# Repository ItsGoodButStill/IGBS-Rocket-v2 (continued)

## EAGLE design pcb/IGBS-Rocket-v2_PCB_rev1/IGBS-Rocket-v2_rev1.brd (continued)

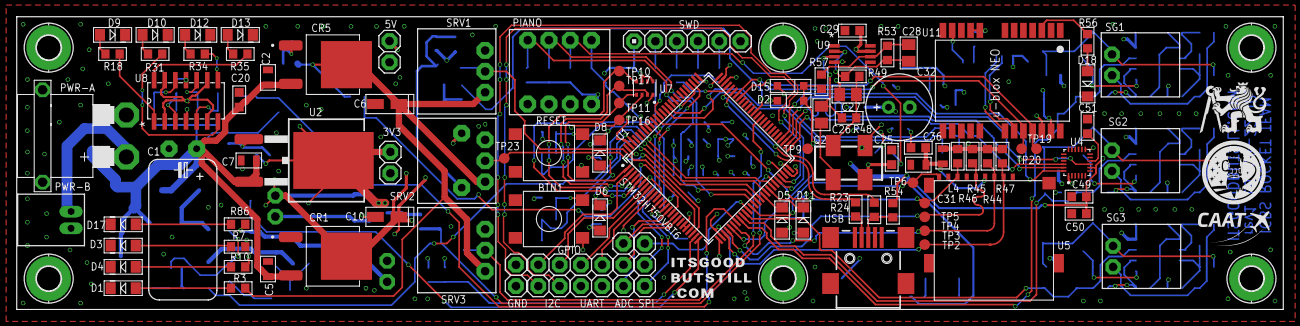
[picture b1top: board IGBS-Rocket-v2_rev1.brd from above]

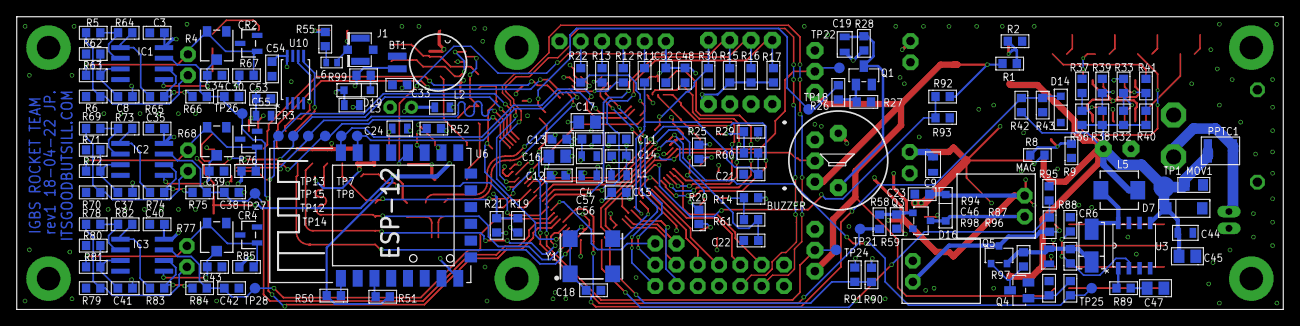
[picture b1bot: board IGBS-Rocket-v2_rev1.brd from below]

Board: 4 copper layers, 151.1 x 34.9 mm, 269 parts (164 on the bottom side), 154 nets.

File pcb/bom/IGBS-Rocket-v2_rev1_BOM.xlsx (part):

IGBS Rocket v2 (rev1)
 | Množství | Sklad | Hodnota | Název | Pouzdro | Součástky | Popis | Výrobce | Cena | Objednací číslo | Odkaz
 | 1 | 0 | STM32H750VBT6 | STM32H750VBT6 | LQFP100-14X14 | U1 | MCU | STM | 300 | Aliexpress | https://www.aliexpress.com/item/1005003610067060.html?spm=a2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
 | 1 | 0 | BMP280 | BMP280 | BMP280 | B1 | Modul - Barometr | Bosch | 21 | Aliexpress | https://www.aliexpress.com/item/32817286611.html?spm=a2g0o.9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
 | 1 | 5 | ESP-12E/F | ESP-12E/F | ESP-12E | U6 | Modul - ESP WiFi | Espressif | 32 | Aliexpress | https://www.aliexpress.com/item/32256161821.html?spm=a2g0o.9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
 | 1 | 1 | GY-NEO6MV2 | GY-NEO6MV2 | GY-NEO6MV2 | B6 | Modul - GPS | U-blox | 68 | Aliexpress | https://www.aliexpress.com/item/1005001635722164.html?spm=a2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
 | 1 | 1 | ICM-20948 | ICM-20948 | ICM-20948 | B2 | Modul - IMU 9-DOF | InvenSense | 471 | Aliexpress | https://www.aliexpress.com/wholesale?catId=0&initiative_id=S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
 | 3 | 5 | BF350 | BF350 | BF350 | B3, B4, B5 | Modul - Tenzometr | čína | 0 | Aliexpress | https://www.aliexpress.com/item/4000907686535.html?spm=a2g0o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
 | 1 | 1 | ENC-03 | ENC-03RC | ENC-03RC | Q2 | Gyroskop (analogový 1-osý) | Murata | 115 | 775-043 | https://www.gme.cz/modul-s-jednoosym-gyroskopem-analog-vystup
 | 1 | 0 | MCP6V51T-E/MS | MCP6V51T-E/MS | MSOP8 | U9 | OP Amp (1 kanál, nulovaný) | Microchip | 43 | 579-MCP6V51T-E/MS | https://cz.mouser.com/ProductDetail/Microchip-Technology/MCP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
 | 1 | 0 | LP324DRG4 | LP324DRG4D14 | SOIC-14 | U8 | OP Amp (4 kanál, low-power) | TI | 16 | 595-LP324DRG4 | https://cz.mouser.com/ProductDetail/Texas-Instruments/LP324D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
 | 3 | 0 | NCV21872DR2G | NCV21872DR2G | SOIC-8 | IC1,IC2,IC3 | OP Amp (2 kanál, precision) | Onsemi | 23 | 863-NCV21872DR2G | https://cz.mouser.com/ProductDetail/onsemi/NCV21872DR2G?qs=s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
 | 1 | 0 | 24MHz | OSCILLATOR | SMD-7X5-4PAD | Y1 | Oscilátor | IQD | 40 | 449-LFSPXO018541REEL | https://cz.mouser.com/ProductDetail/IQD/LFSPXO018541Reel?qs=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
 | 1 | 0 | LM317BD2TG | LM317BD2TG | TO-263-3 | U4 | Regulátor - 3.3 V 1.5A | Onsemi | 57 | 863-LM317BD2TG | https://cz.mouser.com/ProductDetail/onsemi/LM317BD2TG?qs=2Ot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
 | 1 | 0 | LD1117DT50 | LD1117DT50TRDPAK | TO-252-3 | CR1 | Regulátor - LDO 5V 1A | STM | 15 | 511-LD1117DT50-TR | https://cz.mouser.com/ProductDetail/STMicroelectronics/LD111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
 | 1 | 0 | AZ2185D | AZ2185D-ADJTRG1 | TO-252-3 | CR5 | Regulátor - LDO 6V 3A | Diodes Inc. | 12 | 621-AZ2185D-ADJTRG1 | https://cz.mouser.com/ProductDetail/Diodes-Incorporated/AZ21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
 | 1 | 0 | CS5171EDR8G | CS5171EDR8G | SOIC-8 | U3 | DC-DC Boost 12V 1.5 A | Onsemi | 12 | CS5171EDR8G | https://cz.farnell.com/on-semiconductor/cs5171edr8g/dc-dc-co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
 | 1 | 0 | BSS316N-H6327 | MOSFET-NCHANNEL | SOT23-3 | Q3 | Tranzistor (N-MOSFET) | Infineon | 10 | 726-BSS316NH6327XT | https://cz.mouser.com/ProductDetail/Infineon-Technologies/BS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
 | 1 | 0 | BSS314PE H6327 | MOSFET-PCHANNEL | SOT23-3 | Q5 | Tranzistor (P-MOSFET) | Infineon | 10 | 726-BSS314PEH6327XT | https://cz.mouser.com/ProductDetail/Infineon-Technologies/BS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
 | 2 | 0 | BC817 | BC817-16LT1SMD | SOT23-BEC | Q1 | Tranzistor (NPN) | NXP | 5 | 771-BC817-40-T/R | https://cz.mouser.com/ProductDetail/Nexperia/BC817-40215?qs=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
 | 1 | 0 | 1N4148 | DIODESOD123 | SOD-123 | D16 | Dioda | Vishay | 8 | 78-1N4148W-G3-08 | https://cz.mouser.com/ProductDetail/Vishay-Semiconductors/1N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
 | 1 | 0 | SS12 | DIODE SHOTTKY | DO-214 | CR16 | Shottkyho dioda | Onsemi | 9 | 512-SS12 | https://cz.mouser.com/ProductDetail/onsemi-Fairchild/SS12?qs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
 | 3 | 0 | 3V6 | DIODE-ZENER | SOD-123 | D14, D15 | Zenerova dioda 3.6V | NXP | 6 | 771-BZT52-B3V6X | https://cz.mouser.com/ProductDetail/Nexperia/BZT52-B3V6X?qs=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
 | 3 | 0 | TS4040DILT-2.5 | REF2.5 | SOT-23-3 | CR2,CR3,CR4 | Reference 2.5V | STM | 18 | 511-TS4040DILT-2.5 | https://cz.mouser.com/ProductDetail/STMicroelectronics/TS404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
 | 1 | 0 | 10V | VARISTORCN0805 | CT/CN0805 | MOV1 | Varistor | AVX | 9.3800000000000008 | 581-VCUG080100L1DP | https://cz.mouser.com/ProductDetail/Kyocera-AVX/VCUG080100L1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
 | 1 | 0 | TVSSMA | TVSSMA | SMA-DIODE | D7 | TVS (transil) | Diodes Inc. | 11 | 621-SMAJ12AQ-13-F | https://cz.mouser.com/ProductDetail/Diodes-Incorporated/SMAJ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
 | 1 | 0 | 10V/5.5A | PPTC_6V2A | PPTC-1210 | PPTC1 | Resetovatelná pojistka (PPTC) | Bourns | 19 | 652-MF-USML250-2 | https://cz.mouser.com/ProductDetail/Bourns/MF-USML250-2?qs=G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
 | 1 | 0 | red | LED-1206 | LED-1206 | D11 | LED (červená) - app 3 | Kingsbright | 7 | 604-APTR3216SURCK | https://cz.mouser.com/ProductDetail/Kingbright/APTR3216SURCK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
 | 2 | 0 | blue | LED-1206 | LED-1206 | D5 | LED (modrá) - app 1,4 | Kingsbright | 11 | 604-APT3216LVBCD | https://cz.mouser.com/ProductDetail/Kingbright/APT3216LVBC-D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
 | 4 | 0 | orange | LED-1206 | LED-1206 | D9, D10, D12, D13 | LED (oranžová) - baterie | Kingsbright | 6 | 604-APTR3216SECK | https://cz.mouser.com/ProductDetail/Kingbright/APTR3216SECK?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
 | 4 | 0 | green | LED-1206 | LED-1206 | D1, D2, D3, D4 | LED (zelená) - PSU | Kingsbright | 9 | 604-APTR3216CGCK | https://cz.mouser.com/ProductDetail/Kingbright/APTR3216CGCK?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
 | 1 | 0 | yellow | LED-1206 | LED-1206 | D6 | LED (žlutá) - app 2 | Kingsbright | 11 | 604-APTR3216SYC | https://cz.mouser.com/ProductDetail/Kingbright/APTR3216SYC?q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
 | 3 | 0 | 500k | R-TRIMM-SMD | 3.6x3.6x2.0 | R4,R68,R77 | Trimmer (20%) | Bourns | 31 | 81-PVG3A504C01R00 | https://cz.mouser.com/ProductDetail/Bourns/PVG3A504C01R00?qs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
 | 2 | 0 | 100k | R-EU_R0603 | R0603 | R48, R59 | Rezistor (1%) | Bourns | 2 | 652-CR0603-FX-103ELF | https://cz.mouser.com/ProductDetail/Bourns/CR0603-FX-1003ELF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
 | 18 | 0 | 10k | R-EU_R0603 | R0603 | R14, R15, R16, R17, R27, R29, R30, R32, R36, R39, R40, R49, R50, R51, R52 | Rezistor (1%) | Bourns | 2 | 652-CR0603FX-1002ELF | https://cz.mouser.com/ProductDetail/Bourns/CR0603-FX-1002ELF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
 | 2 | 0 | 12k | R-EU_R0603 | R0603 | R38, R42 | Rezistor (1%) | Bourns | 2 | 652-CR0603FX-1202ELF | https://cz.mouser.com/ProductDetail/Bourns/CR0603-FX-1202ELF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
 | 2 | 0 | 150R | R-EU_R0603 | R0603 | R1, R4 | Rezistor (1%) | Vishay | 2 | 71-CRCW0603150RFKEBC | https://cz.mouser.com/ProductDetail/Vishay-Dale/CRCW0603150R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
 | 9 | 0 | 1K | R-EU_R0603 | R0603 | R10, R19, R20, R21, R25, R26, R28, R57 | Rezistor (1%) | Vishay | 2 | 71-CRCW06031K00FKEAC | https://cz.mouser.com/ProductDetail/Vishay-Dale/CRCW06031K00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
 | 6 | 0 | 1K5 | R-EU_R0603 | R0603 | R7, R18, R31, R34, R35, R54 | Rezistor (1%) | Bourns | 2 | 652-CR0603FX-1501ELF | https://cz.mouser.com/ProductDetail/Bourns/CR0603-FX-1501ELF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
 | 1 | 0 | 1K27 | R-EU_R0603 | R0603 | R88 | Rezistor (1%) | Bourns | 2 | 652-CR0603FX-1271ELF | https://cz.mouser.com/ProductDetail/Bourns/CR0603-FX-1271ELF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
 | 2 | 0 | 1K8 | R-EU_R0603 | R0603 | R3, R6 | Rezistor (1%) | Vishay | 2 | 71-CRCW06031K80FKEAC | https://cz.mouser.com/ProductDetail/Vishay-Dale/CRCW06031K80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
 | 3 | 0 | 20k | R-EU_R0603 | R0603 | R65,R74,R83 | Rezistor (1%) | Vishay | 2 | 71-CRCW060320K0FKEAC | https://cz.mouser.com/ProductDetail/Vishay-Dale/CRCW060320K0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
 | 7 | 0 | 22R | R-EU_R0603 | R0603 | R11, R12, R13, R22, R23, R24, R58 | Rezistor (1%) | Bourns | 2 | 652-CR0603FX-22R0ELF | https://cz.mouser.com/ProductDetail/Bourns/CR0603-FX-22R0ELF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
 | 1 | 0 | 240R | R-EU_R0603 | R0603 | R8 | Rezistor (1%) | YAGEO | 2 | 603-RC0603FR-13240RL | https://cz.mouser.com/ProductDetail/YAGEO/RC0603FR-13240RL?q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
 | 1 | 0 | 3k6 | R-EU_R0603 | R0603 | R86 | Rezistor (1%) | Bourns | 2 | 652-CR0603FX-3602ELF | https://cz.mouser.com/ProductDetail/Bourns/CR0603-FX-3602ELF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
 | 1 | 0 | 30k | R-EU_R0603 | R0603 | R94 | Rezistor (1%) | Bourns | 2 | 652-CR0603FX-3002ELF | https://cz.mouser.com/ProductDetail/Bourns/CR0603-FX-3002ELF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
 | 3 | 0 | 330R | R-EU_R0603 | R0603 | R67,R76,R85 | Rezistor (1%) | Bourns | 2 | 652-CR0603FX-3300ELF | https://cz.mouser.com/ProductDetail/Bourns/CR0603-FX-3300ELF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
 | 9 | 0 | 360R | R-EU_R0603 | R0603 | R63,R6,R62,R72,R70,R71,R81,R79,R80 | Rezistor (1%) | Bourns | 2 | 652-CR0603FX-3600ELF | https://cz.mouser.com/ProductDetail/Bourns/CR0603-FX-3600ELF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

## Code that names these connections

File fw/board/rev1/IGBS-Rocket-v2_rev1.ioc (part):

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Mcu.Name=STM32H750VBTx
Mcu.Package=LQFP100
Mcu.UserName=STM32H750VBTx
PA0.GPIOParameters=GPIO_Label
PA0.GPIO_Label=TIM2 CH1 PWM - SERVO1
PA0.Signal=S_TIM2_CH1
PA1.GPIOParameters=GPIO_Label
PA1.GPIO_Label=TIM5 CH2 PWM - SERVO2
PA1.Signal=S_TIM5_CH2
PA10.GPIOParameters=GPIO_Label
PA10.GPIO_Label=USART1 RX - GPS
PA10.Mode=Asynchronous
PA10.Signal=USART1_RX
PA11.Mode=Device_Only
PA11.Signal=USB_OTG_FS_DM
PA12.Mode=Device_Only
PA12.Signal=USB_OTG_FS_DP
PA13\ (JTMS/SWDIO).GPIOParameters=GPIO_Label
PA13\ (JTMS/SWDIO).GPIO_Label=SWDIO
PA13\ (JTMS/SWDIO).Mode=Trace_Asynchronous_SW
PA13\ (JTMS/SWDIO).Signal=DEBUG_JTMS-SWDIO
PA14\ (JTCK/SWCLK).GPIOParameters=GPIO_Label
PA14\ (JTCK/SWCLK).GPIO_Label=SWCLK
PA14\ (JTCK/SWCLK).Mode=Trace_Asynchronous_SW
PA14\ (JTCK/SWCLK).Signal=DEBUG_JTCK-SWCLK
PA2.GPIOParameters=GPIO_Label
PA2.GPIO_Label=ADC2 IN14 - 5V
PA2.Signal=ADCx_INP14
PA3.GPIOParameters=GPIO_Label
PA3.GPIO_Label=ADC2 IN15 - 12V
PA3.Signal=ADCx_INP15
PA4.GPIOParameters=GPIO_Label
PA4.GPIO_Label=SPI1 NSS - SDCARD
PA4.Mode=NSS_Signal_Hard_Output
PA4.Signal=SPI1_NSS
PA5.GPIOParameters=GPIO_Label
PA5.GPIO_Label=SPI1 SCK - SDCARD
PA5.Mode=Full_Duplex_Master
PA5.Signal=SPI1_SCK
PA6.GPIOParameters=GPIO_Label
PA6.GPIO_Label=ADC1 IN3 - ANG-RATE
PA6.Signal=ADCx_INP3
PA7.GPIOParameters=GPIO_Label
PA7.GPIO_Label=SPI1 MOSI - SDCARD
PA7.Mode=Full_Duplex_Master
PA7.Signal=SPI1_MOSI
PA9.GPIOParameters=GPIO_Label
PA9.GPIO_Label=USART1 TX - GPS
PA9.Mode=Asynchronous
PA9.Signal=USART1_TX
PB0.GPIOParameters=GPIO_Label
PB0.GPIO_Label=ADC2 IN9 - GAUG2
PB0.Signal=ADCx_INP9
PB1.GPIOParameters=GPIO_Label
PB1.GPIO_Label=ADC2 IN5 - GAUG3
PB1.Signal=ADCx_INP5
PB10.GPIOParameters=GPIO_Label
PB10.GPIO_Label=I2C2 SCL - AUX
PB10.Mode=I2C
PB10.Signal=I2C2_SCL
PB11.GPIOParameters=GPIO_Label
PB11.GPIO_Label=I2C2 SDA - AUX
PB11.Mode=I2C
PB11.Signal=I2C2_SDA
PB12.GPIOParameters=GPIO_Label
PB12.GPIO_Label=SPI2 NSS - IMU
PB12.Mode=NSS_Signal_Hard_Output
PB12.Signal=SPI2_NSS
PB13.GPIOParameters=GPIO_Label
PB13.GPIO_Label=SPI2 SCK - IMU
PB13.Mode=Full_Duplex_Master
PB13.Signal=SPI2_SCK
PB14.GPIOParameters=GPIO_Label
PB14.GPIO_Label=SPI2 MISO - IMU
PB14.Mode=Full_Duplex_Master
PB14.Signal=SPI2_MISO
PB15.GPIOParameters=GPIO_Label
PB15.GPIO_Label=SPI2 MOSI - IMU
PB15.Mode=Full_Duplex_Master
PB15.Signal=SPI2_MOSI
PB2.GPIOParameters=GPIO_Label
PB2.GPIO_Label=SPI3 MOSI - AUX
PB2.Mode=Full_Duplex_Master
PB2.Signal=SPI3_MOSI
PB3\ (JTDO/TRACESWO).GPIOParameters=GPIO_Label
PB3\ (JTDO/TRACESWO).GPIO_Label=SWO
PB3\ (JTDO/TRACESWO).Mode=Trace_Asynchronous_SW
PB3\ (JTDO/TRACESWO).Signal=DEBUG_JTDO-SWO
PB4\ (NJTRST).GPIOParameters=GPIO_Label
PB4\ (NJTRST).GPIO_Label=SPI1 MISO - SDCARD
PB4\ (NJTRST).Mode=Full_Duplex_Master
PB4\ (NJTRST).Signal=SPI1_MISO
PB6.GPIOParameters=GPIO_Label
PB6.GPIO_Label=I2C1 SCL - INTERN
PB6.Mode=I2C
PB6.Signal=I2C1_SCL
PB7.GPIOParameters=GPIO_Label
PB7.GPIO_Label=I2C1 SDA - INTERN
PB7.Mode=I2C
PB7.Signal=I2C1_SDA
PC0.GPIOParameters=GPIO_Label
PC0.GPIO_Label=ADC3 IN10 - AUX 3
PC0.Signal=ADCx_INP10
PC1.GPIOParameters=GPIO_Label
PC1.GPIO_Label=ADC2 IN11 - 6V
PC1.Signal=ADCx_INP11
PC10.GPIOParameters=GPIO_Label
PC10.GPIO_Label=SPI3 SCK - AUX
PC10.Mode=Full_Duplex_Master
PC10.Signal=SPI3_SCK
PC11.GPIOParameters=GPIO_Label
PC11.GPIO_Label=SPI3 MISO - AUX
PC11.Mode=Full_Duplex_Master
PC11.Signal=SPI3_MISO
PC13.GPIOParameters=GPIO_Label
PC13.GPIO_Label=GPIO AUX - IN2
PC13.Signal=GPIO_Input
PC14-OSC32_IN\ (OSC32_IN).GPIOParameters=GPIO_Label
PC14-OSC32_IN\ (OSC32_IN).GPIO_Label=GPIO AUX - OUT1
PC14-OSC32_IN\ (OSC32_IN).Signal=GPIO_Output
PC15-OSC32_OUT\ (OSC32_OUT).GPIOParameters=GPIO_Label
PC15-OSC32_OUT\ (OSC32_OUT).GPIO_Label=GPIO AUX - OUT2
PC15-OSC32_OUT\ (OSC32_OUT).Signal=GPIO_Output
PC2_C.GPIOParameters=GPIO_Label
PC2_C.GPIO_Label=ADC3 IN0 - AUX 1
PC2_C.Mode=IN0-Single-Ended
PC2_C.Signal=ADC3_INP0
PC3_C.GPIOParameters=GPIO_Label
PC3_C.GPIO_Label=ADC3 IN1 - AUX 2
PC3_C.Mode=IN1-Single-Ended
PC3_C.Signal=ADC3_INP1
PC4.GPIOParameters=GPIO_Label
PC4.GPIO_Label=ADC2 IN4 - BAT
PC4.Signal=ADCx_INP4
PC5.GPIOParameters=GPIO_Label
PC5.GPIO_Label=ADC2 IN8 - GAUG1
PC5.Signal=ADCx_INP8
PC6.GPIOParameters=GPIO_Label
PC6.GPIO_Label=TIM3 CH1 PWM - BUZZER
PC6.Signal=S_TIM3_CH1
PD14.GPIOParameters=GPIO_Label
PD14.GPIO_Label=TIM4 CH3 PWM - SERVO3
PD14.Signal=S_TIM4_CH3
PD5.GPIOParameters=GPIO_Label
PD5.GPIO_Label=USART2 TX - WIFI
PD5.Mode=Asynchronous
PD5.Signal=USART2_TX
PD6.GPIOParameters=GPIO_Label
PD6.GPIO_Label=USART2 RX - WIFI
PD6.Mode=Asynchronous
PD6.Signal=USART2_RX
PD8.GPIOParameters=GPIO_Label
PD8.GPIO_Label=USART3 TX - AUX
PD8.Mode=Asynchronous
PD8.Signal=USART3_TX
PD9.GPIOParameters=GPIO_Label
PD9.GPIO_Label=USART3 RX - AUX
PD9.Mode=Asynchronous
PD9.Signal=USART3_RX
PE1.GPIOParameters=GPIO_Label
PE1.GPIO_Label=GPIO OUT - CTRL 12V
PE1.Signal=GPIO_Output
PE10.GPIOParameters=GPIO_Label
PE10.GPIO_Label=GPIO IN - BTN1
PE10.Signal=GPIO_Input
PE11.GPIOParameters=GPIO_Label,GPIO_ModeDefaultOutputPP
PE11.GPIO_Label=GPIO OUT - LED 1 (RED)
PE11.GPIO_ModeDefaultOutputPP=GPIO_MODE_OUTPUT_OD
PE11.Signal=GPIO_Output
PE12.GPIOParameters=GPIO_Label,GPIO_ModeDefaultOutputPP
PE12.GPIO_Label=GPIO OUT - LED 2 (GREEN)
PE12.GPIO_ModeDefaultOutputPP=GPIO_MODE_OUTPUT_OD
PE12.Signal=GPIO_Output
PE13.GPIOParameters=GPIO_Label,GPIO_ModeDefaultOutputPP
PE13.GPIO_Label=GPIO OUT - LED 3 (BLUE)
PE13.GPIO_ModeDefaultOutputPP=GPIO_MODE_OUTPUT_OD
PE13.Signal=GPIO_Output
PE14.GPIOParameters=GPIO_Label,GPIO_ModeDefaultOutputPP
PE14.GPIO_Label=GPIO OUT - LED 4 (ORANGE)
PE14.GPIO_ModeDefaultOutputPP=GPIO_MODE_OUTPUT_OD
PE14.Signal=GPIO_Output
PE15.GPIOParameters=GPIO_Label
PE15.GPIO_Label=GPIO OUT - MAGNET
PE15.Signal=GPIO_Output
PE2.GPIOParameters=GPIO_Label
PE2.GPIO_Label=SPI4 SCK - BMP
PE2.Mode=Full_Duplex_Master
PE2.Signal=SPI4_SCK
PE3.GPIOParameters=GPIO_Label
PE3.GPIO_Label=GPIO AUX - IN1
PE3.Signal=GPIO_Input
PE4.GPIOParameters=GPIO_Label
PE4.GPIO_Label=SPI4 CS - BMP
PE4.Mode=NSS_Signal_Hard_Output
PE4.Signal=SPI4_NSS
PE5.GPIOParameters=GPIO_Label
PE5.GPIO_Label=SPI4 MISO - BMP
PE5.Mode=Full_Duplex_Master
PE5.Signal=SPI4_MISO
PE6.GPIOParameters=GPIO_Label
PE6.GPIO_Label=SPI4 MOSI - BMP
PE6.Mode=Full_Duplex_Master
PE6.Signal=SPI4_MOSI
PE7.GPIOParameters=GPIO_Label
PE7.GPIO_Label=GPIO IN - SDCARD DETECT
PE7.Signal=GPIO_Input
PE8.GPIOParameters=GPIO_Label
PE8.GPIO_Label=GPIO IN - PIANO3
PE8.Signal=GPIO_Input
PE9.GPIOParameters=GPIO_Label
PE9.GPIO_Label=GPIO IN - PIANO4
PE9.Signal=GPIO_Input
PH0-OSC_IN\ (PH0).Mode=HSE-External-Oscillator
PH0-OSC_IN\ (PH0).Signal=RCC_OSC_IN
PH1-OSC_OUT\ (PH1).Mode=HSE-External-Oscillator
PH1-OSC_OUT\ (PH1).Signal=RCC_OSC_OUT
RCC.HSE_VALUE=24000000
RCC.SYSCLKFreq_VALUE=480000000
RCC.SYSCLKSource=RCC_SYSCLKSOURCE_PLLCLK
board=custom

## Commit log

2022-02-13 PCB CAD - update
2022-02-13 + photos from 2021 session * README.md update
2022-02-16 + schematics done
2022-02-18 * schematics is validated and ready for layout
2022-02-20 + PCB - BOM created * minor adjustments to PCB schematics
2022-02-27 + PCB BOM
2022-03-04 * PCB layout 30 % T strain-gauge modules to sch
2022-03-06 + PCB schematic is DONE + BOM (Mouser) is DONE
2022-03-11 * PCB: 12V regulator added, P-FET HSS is now last missing part
2022-03-13 + PCB schematics is DONE (added 12V BOOST + 3 servos)
2022-03-23 + PCB layout done (DXF, STEP, BRD, PNG)
2022-03-23 * minor fixes
2022-03-25 * PCB schematics upgrade (removed all modules) last thing GPS part needs to be done
2022-03-26 + PCB layout DONE + PCB 3D model is ready
2022-03-26 * 3D model of hole minor fix
2022-03-26 + PCB 3D IPT
2022-03-27 + PCB layout checking and cleaning up (silkscreen)
2022-03-27 + PCB layout check done (routing follows)
2022-04-01 * PCB routing 25 % done
2022-04-03 + PCB routing signals 90 %
2022-04-09 * PCB layout last 2 layers
2022-04-10 * PCB layout fixes
2022-04-18 + PCB layout is complete -> GERBERS are ready
